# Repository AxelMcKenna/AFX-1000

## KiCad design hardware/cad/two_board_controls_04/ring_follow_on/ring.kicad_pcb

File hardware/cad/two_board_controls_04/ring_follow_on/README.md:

# Screw-retained RGB ring and populated emitter board

**Guide correction:** use `../connected-guide-r1` final guide exports and `../connected_guide.scad` integration wrappers. Earlier guide exports remain historical because their ring relief left a loose central island. The final guides are each one connected solid; all50 button seats remain verified.

Eight Kingbright APTF1616LSEEZGKQBKC common-anode RGB emitters align to the existing eight optical rods at radius 24 mm about (244,78). Exact primary package, polarity and recommended land geometry are retained in `APTF1616LSEEZGKQBKC.pdf`. Pin 1 is anode, pins 2/3/4 are red/green/blue cathodes. Each cathode branch includes a Yageo RC0603FR-071KP 1 kΩ resistor; the 24 resistors use the existing KiCad 0603 land pattern. Manufacturer resistor dimensions/rating are retained in `Yageo-RC-P.pdf` and the exact part is documented at https://www.yageogroup.com/component-documentation/download/specsheet/RC0603FR-071KP .

Only the existing three ring sink channels 93–95 are used. The three channels each feed eight resistor/LED branches; there are no new independently addressable ring segments. At the existing approximately 3 mA channel setting, equal sharing would give 0.375 mA per LED. The resistors reduce imbalance but do not guarantee equal brightness. Actual forward-voltage bins, diffuser material, ambient visibility, color balance and current-sink compliance must be tested. Native connectivity and DRC are not powered optical acceptance.

Board bottom/top are Z39.3/40.9. LED maximum envelope top is Z41.8; the retained optical rod bottoms are Z42.0. The board's main outer radius is 29.5 mm, with three mounting lobes; inner radius is 17.8 mm. Three existing-pattern M2 fasteners are newly located at radius 28.5 mm, angles 22.5°,157.5°,286°. These are explicit new lid holes, not presumed PCB holes. Use M2×12 screws, head OD≤4.5 mm, AF4×1.6 mm nuts, and 0.5 mm washers. Screw heads bear on the new 2 mm lens ears at Z47.6; nuts occupy Z37.2–38.8. Printed frame posts clamp the board against the washers. The clear lens is captured by the same three screws; no adhesive is relied upon.

The old lid treats the eight ring-light openings as generic knob holes, producing Ø9.5 mm holes rather than the intended Ø3 mm. The new lid repairs only these holes using a 2D annular fill and recuts Ø3 mm receivers. The old guide already has explicit Ø3.2 rod holes; the new guide additionally clears the actual carrier/board outline by 0.2 mm. Exact symmetric-difference checks prove all geometry outside declared ring aperture/mount/carrier masks is preserved, including earlier display, selector, meter and bank changes.

`native-r6` passes nine empty clearance/preservation checks, three positive retention/material-restoration checks, and eight printable full/split exports. `pcb-native-r5/review.json` records zero native KiCad violations/opens and verifies every emitter/resistor/wire net group. `wiring.csv` maps four leads to the actual integrated signal board. Integration wrappers: `tbh06_ring_installed()`, `tbh06_lid_variant()`, `tbh06_guide_variant()`.

Failed artifacts remain historical: the original annular board hit scene-holder posts; an attachment arm hit one resistor solder reserve; a whole-boundary retention intersection and the original near-coincident lid fill produced invalid facets. Bounded contact probes and a 2D annular fill corrected these findings. A CGAL lid diagnostic timed out at 60 seconds and was not repeated; the repaired Manifold lid passed a bounded probe before the full batch. Final source bindings are in `checkpoint-sha256.json` and `verification.json`.

Receiving gates: actual PCB thickness, printed pocket/rod clearances, screw/nut dimensions, usable mounting torque, clear optical material, solder insulation, and complete wire routing/strain relief. The local four-wire reserves extend only 2.5 mm below the board. This is a modeled assembly candidate, not fabrication release or whole-unit acceptance.

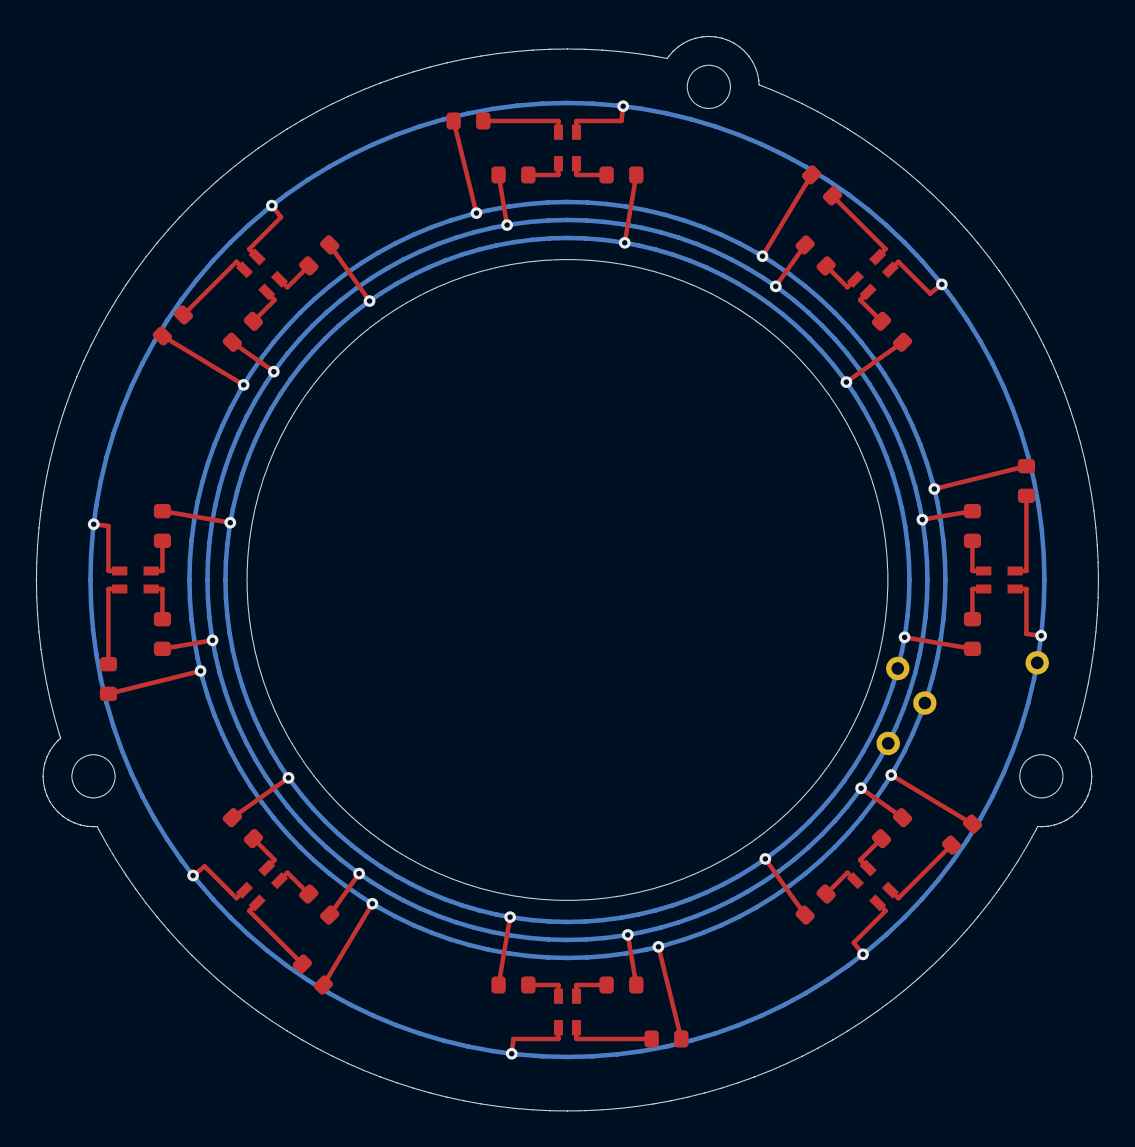
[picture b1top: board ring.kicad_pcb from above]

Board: 2 copper layers, 59.0 x 59.7 mm, 39 parts (0 on the bottom side), 28 nets.

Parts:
D1, D2, D3, D4, D5, D6, D7, D8: APTF1616LSEEZGKQBKC; RGB1616
H1, H2, H3: M2
R1, R2, R3, R4, R5, R6, R7, R8, R9, R10, R11, R12, R13, R14, R15, R16, R17, R18, R19, R20, R21, R22, R23, R24: RC0603FR-071KP; R0603
W1: ANODE_5V; Wire
W2: RING_RED_93; Wire
W3: RING_GREEN_94; Wire
W4: RING_BLUE_95; Wire

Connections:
ANODE_5V: D1.1, D2.1, D3.1, D4.1, D5.1, D6.1, D7.1, D8.1, W1.1
BRANCH_0_0: D1.2, R1.1
BRANCH_0_1: D1.3, R2.2
BRANCH_0_2: D1.4, R3.2
BRANCH_1_0: D2.2, R4.1
BRANCH_1_1: D2.3, R5.2
BRANCH_1_2: D2.4, R6.2
BRANCH_2_0: D3.2, R7.1
BRANCH_2_1: D3.3, R8.2
BRANCH_2_2: D3.4, R9.2
BRANCH_3_0: D4.2, R10.1
BRANCH_3_1: D4.3, R11.2
BRANCH_3_2: D4.4, R12.2
BRANCH_4_0: D5.2, R13.1
BRANCH_4_1: D5.3, R14.2
BRANCH_4_2: D5.4, R15.2
BRANCH_5_0: D6.2, R16.1
BRANCH_5_1: D6.3, R17.2
BRANCH_5_2: D6.4, R18.2
BRANCH_6_0: D7.2, R19.1
BRANCH_6_1: D7.3, R20.2
BRANCH_6_2: D7.4, R21.2
BRANCH_7_0: D8.2, R22.1
BRANCH_7_1: D8.3, R23.2
BRANCH_7_2: D8.4, R24.2
RING_BLUE_95: R3.1, R6.1, R9.1, R12.1, R15.1, R18.1, R21.1, R24.1, W4.1
RING_GREEN_94: R2.1, R5.1, R8.1, R11.1, R14.1, R17.1, R20.1, R23.1, W3.1
RING_RED_93: R1.2, R4.2, R7.2, R10.2, R13.2, R16.2, R19.2, R22.2, W2.1

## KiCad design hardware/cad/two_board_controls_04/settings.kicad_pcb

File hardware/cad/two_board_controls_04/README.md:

# TBH04 — BPM and selector carrier checkpoint

This adds actual removable mounting for three Kingbright SA36-11YWA digits and both selected C&K selector switches. It preserves the TBH01 r6 shell and main PCB positions. The new lid and guide variants have six added screw holes/reliefs; the original r6 lid does not mount these parts. This is an unpowered mechanical fit candidate, not a whole-unit fabrication or functional release. Panel LED emitters/carriers remain separate unfinished work.

## BPM carrier

`display.scad` supplies a bottom tray and separate top bezel. Three digits are at X152/160/168, Y31: **8.0 mm pitch**, replacing the old nominal touching 7.5 mm pitch. The manufacturer's ±0.25 mm body tolerance gives a maximum combined width of 23.75 mm and at least 0.25 mm between adjacent maximum-width bodies. The 24 mm panel opening and 23.2 mm bezel window are retained/defined respectively; segment visibility still needs a physical optical check. Maximum package height is 8.75 mm. The tray floor is Z33.8 and bezel underside Z42.8, giving a 9 mm pocket.

This is a directly wired insulating holder, not a fictional PCB. Thirty Ø1.3 mm lead bores follow the actual two-column 5.08 mm by five-row 2.54 mm pattern. Seat each display at the tray floor. Select thin insulating shims individually after measuring the body height; target 0.05–0.15 mm vertical freedom without preload. Do not use the screws to crush the displays. The nominal pocket leaves 0.25–0.75 mm total height clearance across the stated package tolerance. Pin tips and insulated joints must remain within the stated envelopes and must not load the housing or PCB below.

Two M2×16 screws with head diameter ≤4.5 mm fasten from the lid exterior into two M2 nuts (AF≤4.0 mm, thickness≤1.6 mm) in the tray's underside pockets. No washers are included in this exact screw stack. Under-head Z45.6 gives screw tips at29.6; nuts occupy31.9–33.5. Hand-tighten only. Mount coordinates are **(160,19), (160,43)**. The tray is 25.4×30×11 mm; bezel25.4×30×0.8 mm. Print the small complete tray/bezel first as the fit sample.

Solder the wires with the displays outside the printed carrier; insulate joints, then feed the leads/wires through the tray. No soldering iron should touch printed plastic. `display-wiring.csv` maps all24 cathodes and six common-anode pins to the current integrated main PCB's D_J3004/D_J3005 headers, checked against the source net assignments. Multiple anodes at one supply pin require a proper splice/distribution connection; the CSV is not permission to cram several wires into one crimp. Full harness conductor/connector/splice selection remains open.

## Selector carriers and real breakout boards

The two **16×23×1.6 mm** breakout PCBs are editable KiCad candidates:

- `settings.kicad_pro`: C&K JS202011CQN, six through-hole switch lands, each routed to its own W1–W6 wire pad.
- `release.kicad_pro`: C&K JS203011SCQN, eight surface-mount switch lands, each routed to its own W1–W8 wire pad.

All poles are preserved; no switch terminals are tied together on these breakouts. `selector-contract.json` records exact terminal-to-wire identities. The breakout designs must be connected to the existing control-input circuit with verified switch continuity/position mapping. A one-to-one breakout does not establish which switch position the firmware should call Default/User or Release mode. Native KiCad DRC records zero violations and zero opens for each board; `pcb-native-r2/review.json` also verifies every net's pad identities. These simple pass-through boards have no standalone schematic/ERC claim. Exact chosen switch variant, current land-pattern/stencil acceptance, copper/process selection and assembly inspection remain release gates.

Both use the same printed bracket, two spacers joined above the switch body. The board is clamped between the bracket and underside washers/nuts. Each uses two M2×10 screws, headOD≤4.5 mm, two 0.5 mm washersOD≤4.5 mm and two M2 nutsAF≤4.0×1.6 mm. Head undersideZ45.6, tipZ35.6, nutZ36.0–37.6, washerZ37.6–38.1, PCBZ38.1–39.7, spacerZ39.7–43.6. Hand-tighten, avoiding board bending.

Mounts: settings **(307,17.5),(307,36.5)**; release **(316,44.5),(316,63.5)**. Board centers remain(307,27)/(316,54). The new top-of-PCB datum is **Z39.7**, correcting the old reserve: atZ37.9 the actuator stopped below the cap socket. Nominal3.5 mm body+2 mm actuator now gives actuator top45.2 and **1.6 mm overlap** with the retained cap socket beginning43.6. Verify actual socket engagement, sliding stroke and cap retention with purchased parts; a loose printed cap needs a qualified removable retention method. Do not glue the moving actuator to the switch body.

The displayed switch models are bounded reference geometry, not supplier STEP models. The body allowance is0.2 mm per side and0.2 mm above nominal height. Through-hole leads have3.6 mm downward allowance; SMT leads are separately bounded. The six collision checks include main-board component/lead envelopes, shell, rear plate, button holders, lid join bars, screw heads, guide and lid. Washer-to-PCB contact uses only the existing-style0.01 mm seating-plane guard.

## Printing and assembly

Use `print/` from the delivery package. Print one tray, one bezel and two selector brackets. Use either the one-piece lid/guide or their corresponding left/right variants; preserve the r6 split joining hardware. Geometry remains millimetres at100% scale. The carrier parts themselves fit a small print bed. The case-size limits from r6 still apply. Printer/material settings are not qualified here. Inspect the0.6 mm display side walls,0.8 mm bezel, nut pockets and lead holes in the slicer; measure bores rather than scaling whole parts.

Assemble and test the small carriers first. Install the selector switches on their breakouts and inspect every joint before installing them in plastic. Check pin numbering from the manufacturer terminal1 mark. Route and secure wires independently so their weight cannot pull the switch or display leads. Attach the carrier assemblies to the new lid and then check the complete unpowered assembly. The earlier main-board supports and shell are unchanged.

## Sources and evidence

- Kingbright primary drawing: https://www.kingbrightusa.com/images/catalog/SPEC/SA36-11YWA.pdf (retained source at `../two_board_print_03/reference/SA36-11YWA.pdf`). Package/pin drawing visually reviewed.
- C&K primary current source: https://www.littelfuse.com/assetdocs/littelfuse-c-k-slide-js-series-datasheet?assetguid=aba42b08-0d2c-423b-813d-a2faa5a3bb14 . Official direct download returned403; the manufacturer-authored22Sep2022 PDF is retained at `reference/ck-js.pdf` from the LCSC mirror. Page4 was visually reviewed for both exact variants; current official2026 extracted dimensions agree. Current manufacturer drawing/process acceptance remains a fabrication gate.
- `verification.json`: display source hashes, seven empty clearance cases, two positive retention cases and printable mesh records.
- `selector-verification.json`: current selector source hashes, six empty clearance cases, positive board retention and print exports.
- `pcb-native-r2/`: both native DRC outputs, rendered SVG copper and exact pad/net identity review.
- `display-wiring-review.json`: current main-PCB and channel-map source bindings.

Earlier failed geometry outputs are retained. Display r1 had an insufficient guide relief; r2/r3 exposed a tangent pillar/wall joint. The final design uses overlapping necks and passed a controlled export before fresh checks. The first shortened-neck trial intersected the maximum-size digit by0.125 mm and was corrected. Early selector hardware was too close to solder pads; increasing board length and mount spacing removed actual courtyard/washer conflicts. No failed export is delivered.

The original sealed r6/TBH03 files were not changed. Full LED carrier design, full harness routing, installed thermal assembly, measured fit, switch feel, optical visibility and powered operation are not established by this checkpoint.

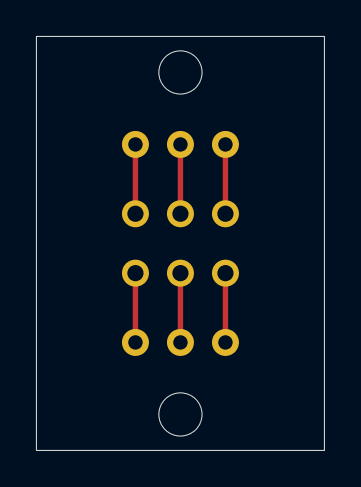
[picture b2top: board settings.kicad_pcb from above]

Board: 2 copper layers, 16.0 x 23.0 mm, 9 parts (0 on the bottom side), 6 nets.

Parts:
H1, H2: M2
SW1: JS202011CQN
W1: SW_PIN_1; WirePad
W2: SW_PIN_2; WirePad
W3: SW_PIN_3; WirePad
W4: SW_PIN_4; WirePad
W5: SW_PIN_5; WirePad
W6: SW_PIN_6; WirePad

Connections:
SW_PIN_1: SW1.1, W1.1
SW_PIN_2: SW1.2, W2.1
SW_PIN_3: SW1.3, W3.1
SW_PIN_4: SW1.4, W4.1
SW_PIN_5: SW1.5, W5.1
SW_PIN_6: SW1.6, W6.1

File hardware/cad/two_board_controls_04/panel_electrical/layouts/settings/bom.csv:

Reference,Part_or_value,Footprint,Source,Note
SW1,JS202011CQN,TBH04:JS202011CQN,https://www.littelfuse.com/assetdocs/littelfuse-c-k-slide-js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,Contact function is a separate manufacturer/firmware-bound state contract
W1,SW_PIN_1,TBH04:WirePad,,Direct-solder external wire pad; mating/routing contract separate
W2,SW_PIN_2,TBH04:WirePad,,Direct-solder external wire pad; mating/routing contract separate
W3,SW_PIN_3,TBH04:WirePad,,Direct-solder external wire pad; mating/routing contract separate
W4,SW_PIN_4,TBH04:WirePad,,Direct-solder external wire pad; mating/routing contract separate
W5,SW_PIN_5,TBH04:WirePad,,Direct-solder external wire pad; mating/routing contract separate
W6,SW_PIN_6,TBH04:WirePad,,Direct-solder external wire pad; mating/routing contract separate
H1,M2,TBH04:M2,,Mechanical NPTH mount; no electrical pin
H2,M2,TBH04:M2,,Mechanical NPTH mount; no electrical pin
